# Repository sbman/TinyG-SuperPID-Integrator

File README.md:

# TinyG-SuperPID-Integrator
 A schematic and PCB design to integrate TinyG with SuperPID

# TinyG Settings
$p1                                                                    
[p1frq] pwm frequency               100 Hz
[p1csl] pwm cw speed lo            5000 RPM
[p1csh] pwm cw speed hi           30000 RPM
[p1cpl] pwm cw phase lo           0.833 [0..1]
[p1cph] pwm cw phase hi           0.000 [0..1]
[p1wsl] pwm ccw speed lo           1000 RPM
[p1wsh] pwm ccw speed hi           2000 RPM
[p1wpl] pwm ccw phase lo          0.125 [0..1]
[p1wph] pwm ccw phase hi          0.200 [0..1]
[p1pof] pwm phase off             0.833 [0..1]

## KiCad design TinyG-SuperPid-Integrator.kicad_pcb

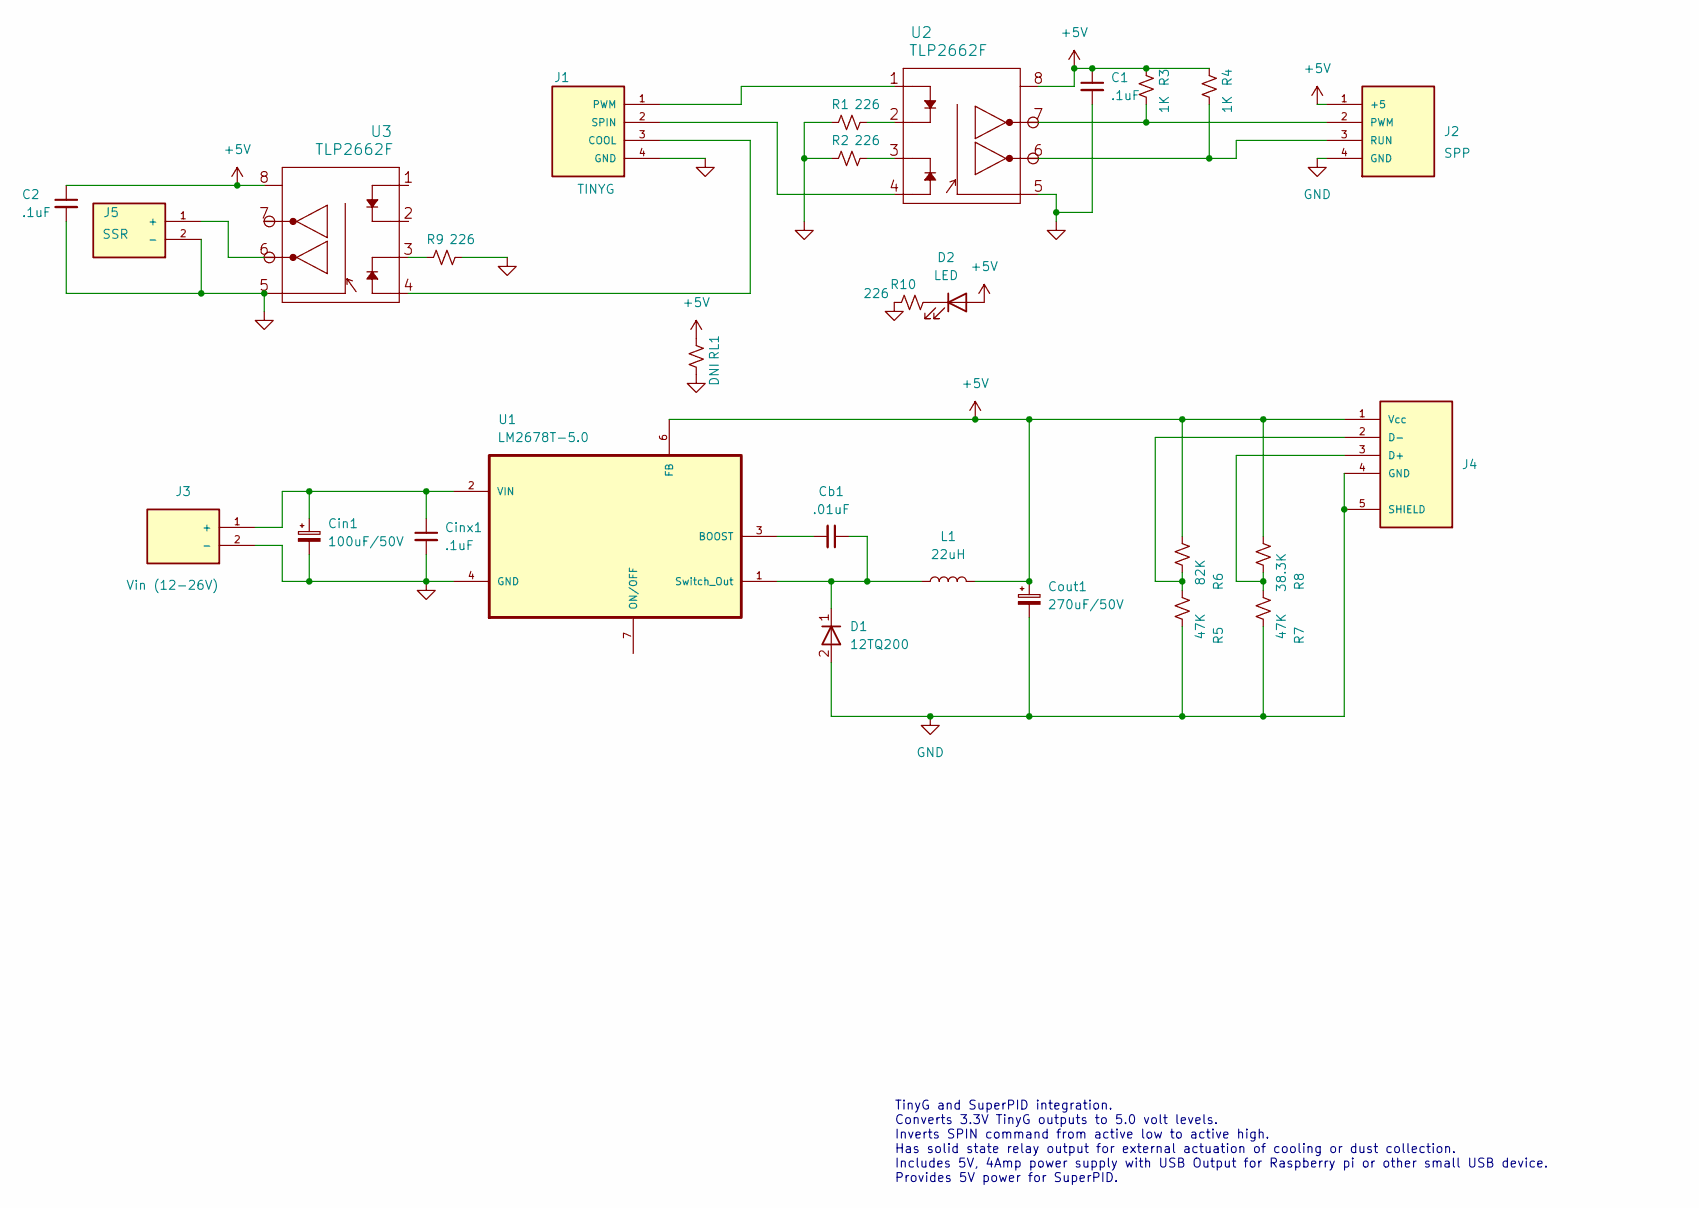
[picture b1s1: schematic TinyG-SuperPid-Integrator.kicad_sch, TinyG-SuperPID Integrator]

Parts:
C1, C2: .1uF; C_Disc_D3.8mm_W2.6mm_P2.50mm; Digikey 445-173588-1-ND
Cb1: .01uF; C_Disc_D3.8mm_W2.6mm_P2.50mm; Digikey 445-173172-1-ND
Cin1: 100uF/50V; CP_Radial_D8.0mm_P3.50mm; Digikey 399-6119-ND
Cinx1: .1uF; C_Disc_D3.8mm_W2.6mm_P2.50mm; Digikey 445-173588-1-ND
Cout1: 270uF/50V; CP_Radial_D10.0mm_P5.00mm; Digikey 399-ESY277M050AH4AA-ND
D1: 12TQ200; TO-220-2_Vertical; Digikey 1655-1003-ND
D2: LED; LED_D5.0mm
J1: TINYG; CUI_TB001-500-04BE; Digikey 102-6136-ND
J2: SPP; CUI_TB001-500-04BE; Digikey 102-6136-ND
J3: Vin (12-26V); CUI_TB001-500-02BE; Digikey 102-6134-ND
J4: UJ2-AH-4-TH; CUI_UJ2-AH-4-TH; PART_REV 1.0; Digikey 102-3994-ND
J5: SSR; CUI_TB001-500-02BE; Digikey 102-6134-ND
L1: 22uH; L_Radial_D16.8mm_P12.07mm_Vishay_IHB-1; Digikey 732-7163-ND
R1, R2, R9, R10: 226; MRS25000C2260FCT00; Digikey BC4072CT-ND
R3, R4: 1K; MRS25000C2260FCT00; Digikey BC3325CT-ND
R5, R7: 47K; MRS25000C2260FCT00; Digikey BC4178CT-ND
R6: 82K; MRS25000C2260FCT00; Digikey BC4265CT-ND
R8: 38.3K; MRS25000C2260FCT00; Digikey BC4145CT-ND
RL1: DNI; R_Axial_DIN0309_L9.0mm_D3.2mm_P12.70mm_Horizontal; Digikey BC4072CT-ND
U1: LM2678T-5.0; TO127P457X1016X2052-7P; MPN LLM2678T-5.0
U2, U3: TLP2662F; Digikey TLP2662(F)-ND

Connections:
+5V: C1.1, C2.1, Cout1.1, D2.2 (A), J2.1 (+5), J4.1 (Vcc), L1.2, R3.2, R4.2, R6.2, R8.2, RL1.2, U1.6 (FB), U2.8 (Vcc), U3.8 (Vcc)
GND: C1.2, C2.2, Cin1.2, Cinx1.2, Cout1.2, D1.2 (A), J1.4 (GND), J2.4 (GND), J3.2 (-), J4.4 (GND), J4.5 (SHIELD), J5.2 (-), R1.2, R2.2, R5.1, R7.1, R9.1, R10.2, RL1.1, U1.4 (GND), U2.5 (GND), U3.5 (GND)
unnamed: Cb1.1, D1.1 (K), L1.1, U1.1 (Switch_Out)
unnamed: Cb1.2, U1.3 (BOOST)
unnamed: Cin1.1, Cinx1.1, J3.1 (+), U1.2 (VIN)
unnamed: D2.1 (K), R10.1
unnamed: J1.1 (PWM), U2.1 (A1)
unnamed: J1.2 (SPIN), U2.4 (A2)
unnamed: J1.3 (COOL), U3.4 (A2)
unnamed: J2.2 (PWM), R3.1, U2.7 (O1)
unnamed: J2.3 (RUN), R4.1, U2.6 (O2)
unnamed: J4.2 (D-), R5.2, R6.1
unnamed: J4.3 (D+), R7.2, R8.1
unnamed: J5.1 (+), U3.6 (O2)
unnamed: R1.1, U2.2 (C1)
unnamed: R2.1, U2.3 (C2)
unnamed: R9.2, U3.3 (C2)

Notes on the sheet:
TinyG and SuperPID integration. Converts 3.3V TinyG outputs to 5.0 volt levels. Inverts SPIN command from active low to active high. Has solid state relay output for external actuation of cooling or dust collection. Includes 5V, 4Amp power supply with USB Output for Raspberry pi or other small USB 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

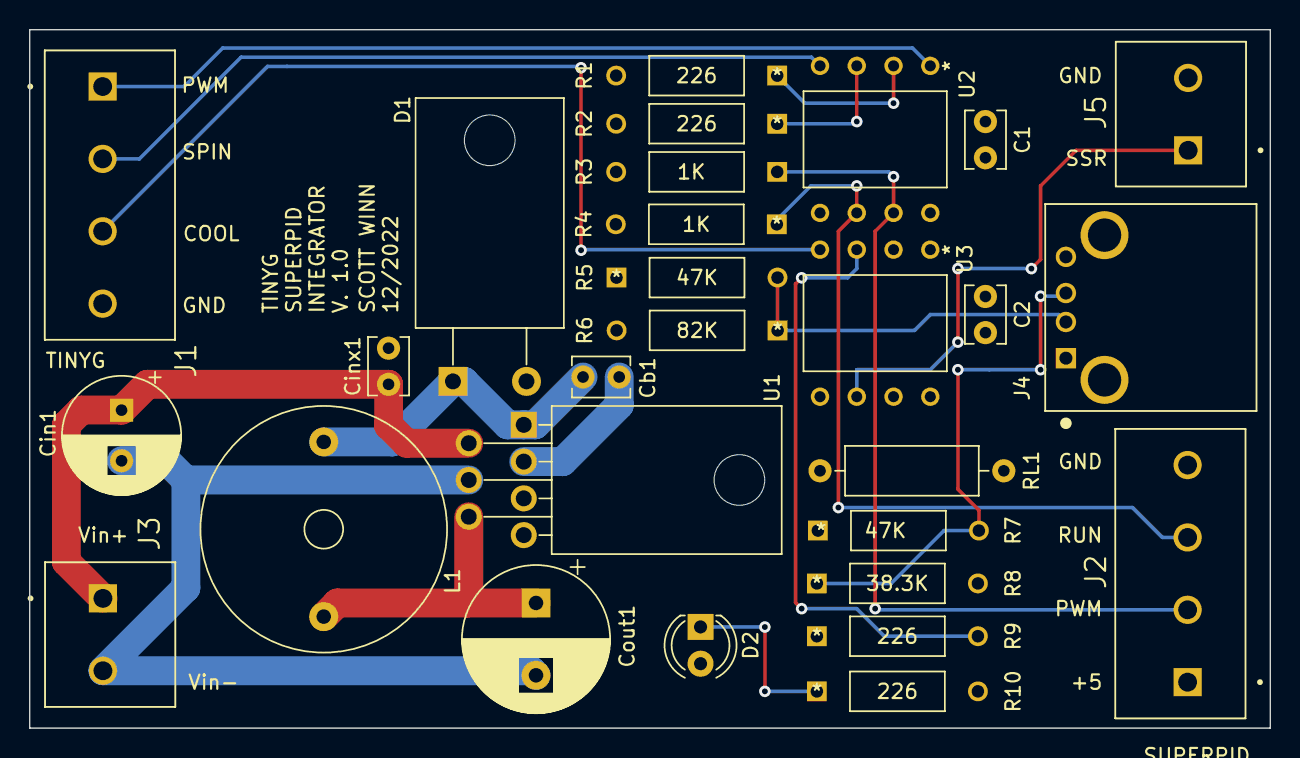
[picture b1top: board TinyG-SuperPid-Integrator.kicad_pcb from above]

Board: 4 copper layers, 85.7 x 48.3 mm, 28 parts (0 on the bottom side), 17 nets.

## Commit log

2022-12-13 Initial commit
    Incomplete, need USB connector.
2022-12-13 Completed schematic, first Rev of PCB layout complete.
    PCB Layout complete
2022-12-14 Fixed backwards diode on U2, straightened internal plane boundaries (aesthetic)
2022-12-14 Added power LED, load resistor. Updated power supply layout.
    Updated layout of power supply to shorten distances between L1, Cout, Cin, and Cb1. Added power LED indicator and pads for a small load resistor to stabilize the switching PS if needed.
2022-12-19 Updated layout of PS, generated Gerber output
    PCB Update, gerber files
2022-12-31 Added settings to readme.

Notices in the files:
parts and their libraries:
Copyright 2021 Accelerated Designs. All rights reserved.
